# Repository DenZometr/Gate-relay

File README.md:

Реле для контроля и управления автоматическими воротами.

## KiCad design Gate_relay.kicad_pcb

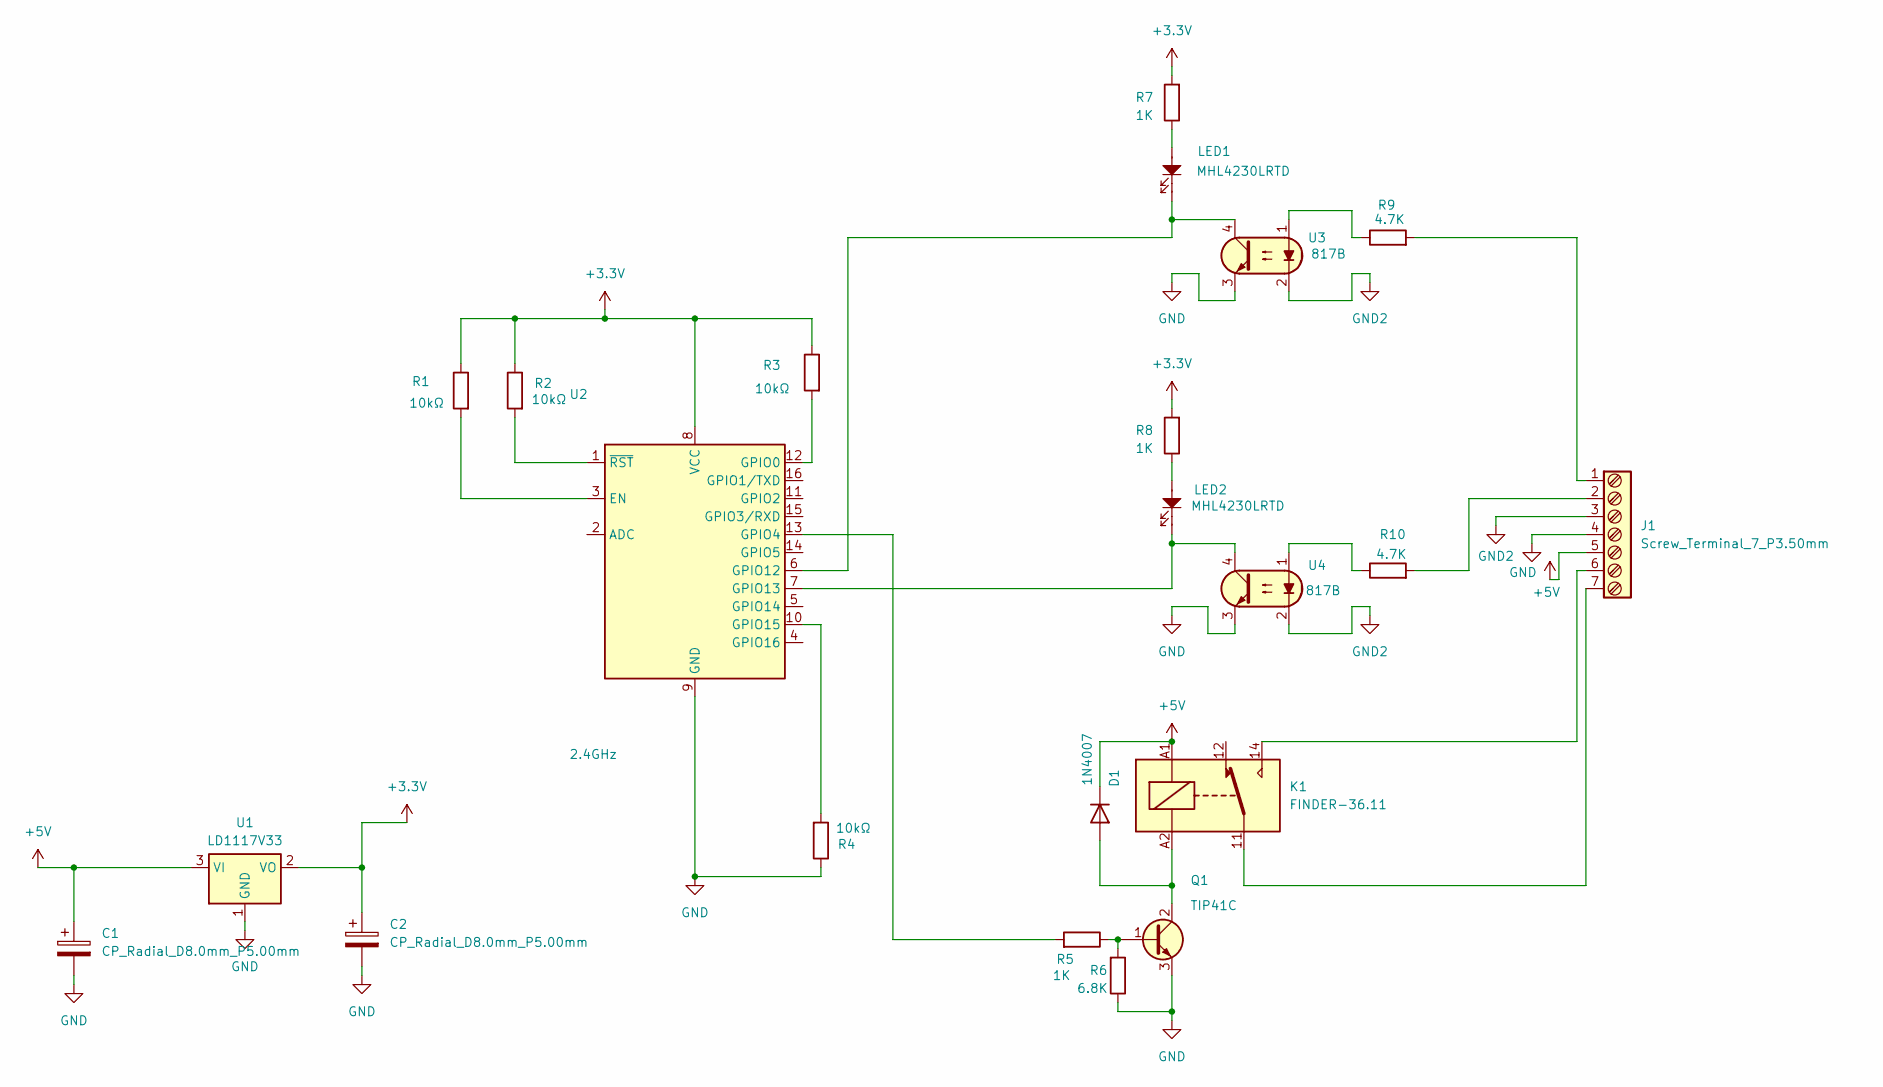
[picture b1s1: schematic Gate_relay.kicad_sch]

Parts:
C1, C2: CP_Radial_D8.0mm_P5.00mm
D1: 1N4007; D_A-405_P5.08mm_Vertical_AnodeUp; VOLTAGE - FORWARD(VF@IF) 1.1V@1A; VOLTAGE - DC REVERSE(VR) 1kV; MANUFACTURER PART 1N4007; LCSC PART NAME 1kV 1A
J1: Screw_Terminal_7_P3.50mm; TerminalBlock_Xinya_XY308-2.54-7P_1x07_P2.54mm_Horizontal
K1: FINDER-36.11; Relay_SPDT_Finder_36.11
LED1, LED2: MHL4230LRTD; LED_D5.0mm; FORWARD VOLTAGE (VF) 1.8V~2.4V; MANUFACTURER PART MHL4230LRTD; LCSC PART NAME F4直插红色雾状发红色光
Q1: TIP41C; TO-220-3_Vertical_BCE; MANUFACTURER PART TIP41C; LCSC PART NAME NPN 电流:6A 耐压:100V
R1, R2, R3, R4: 10kΩ; R_Axial_DIN0204_L3.6mm_D1.6mm_P2.54mm_Vertical; TOLERANCE ±1%; VOLTAGE-SUPPLY(MAX) 250V; MANUFACTURER PART MFR0W4F1002A50; LCSC PART NAME 10kΩ ±1% 250mW 金属膜电阻 铜脚，圆柱状直插
R5, R7: 1K; R_Axial_DIN0204_L3.6mm_D1.6mm_P2.54mm_Vertical
R6: 6.8K; R_Axial_DIN0204_L3.6mm_D1.6mm_P2.54mm_Vertical
R8: 1K; R_Axial_DIN0204_L3.6mm_D1.6mm_P7.62mm_Horizontal
R9, R10: 4.7K; R_Axial_DIN0204_L3.6mm_D1.6mm_P2.54mm_Vertical
U1: LD1117V33; TO-220-3_Vertical
U2: 2.4GHz; ESP-07; OPERATING VOLTAGE 3.3V; MANUFACTURER PART ESP-07; LCSC PART NAME 802.11b/g/n模块
U3, U4: 817B; DIP-4_W7.62mm_LongPads; VOLTAGE - FORWARD(VF) 1.2V; ISOLATION VOLTAGE(VRMS) 5kV; MANUFACTURER PART 817B; LCSC PART NAME DC输入

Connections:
+3.3V: C2.1, R1.2, R2.2, R3.2, R7.1, R8.1, U1.2 (VO), U2.8 (VCC)
+5V: C1.1, D1.1 (K), J1.5, K1.A1, U1.3 (VI)
GND: C1.2, C2.2, J1.4, Q1.3 (E), R4.2, R6.2, U1.1 (GND), U2.9 (GND), U3.3, U4.3
GND2: J1.3, U3.2, U4.2
unnamed: D1.2 (A), K1.A2, Q1.2 (C)
unnamed: J1.1, R9.1
unnamed: J1.2, R10.1
unnamed: J1.6, K1.14
unnamed: J1.7, K1.11
unnamed: LED1.2, R7.2
unnamed: LED2.2, R8.2
unnamed: Q1.1 (B), R5.2, R6.1
unnamed: R9.2, U3.1
unnamed: R10.2, U4.1
unnamed: R1.1, U2.3 (EN)
unnamed: R3.1, U2.12 (GPIO0)
unnamed: R5.1, U2.13 (GPIO4)
unnamed: LED1.1, U2.6 (GPIO12), U3.4
unnamed: LED2.1, U2.7 (GPIO13), U4.4
unnamed: R4.1, U2.10 (GPIO15)
unnamed: R2.1, U2.1 (~RST)

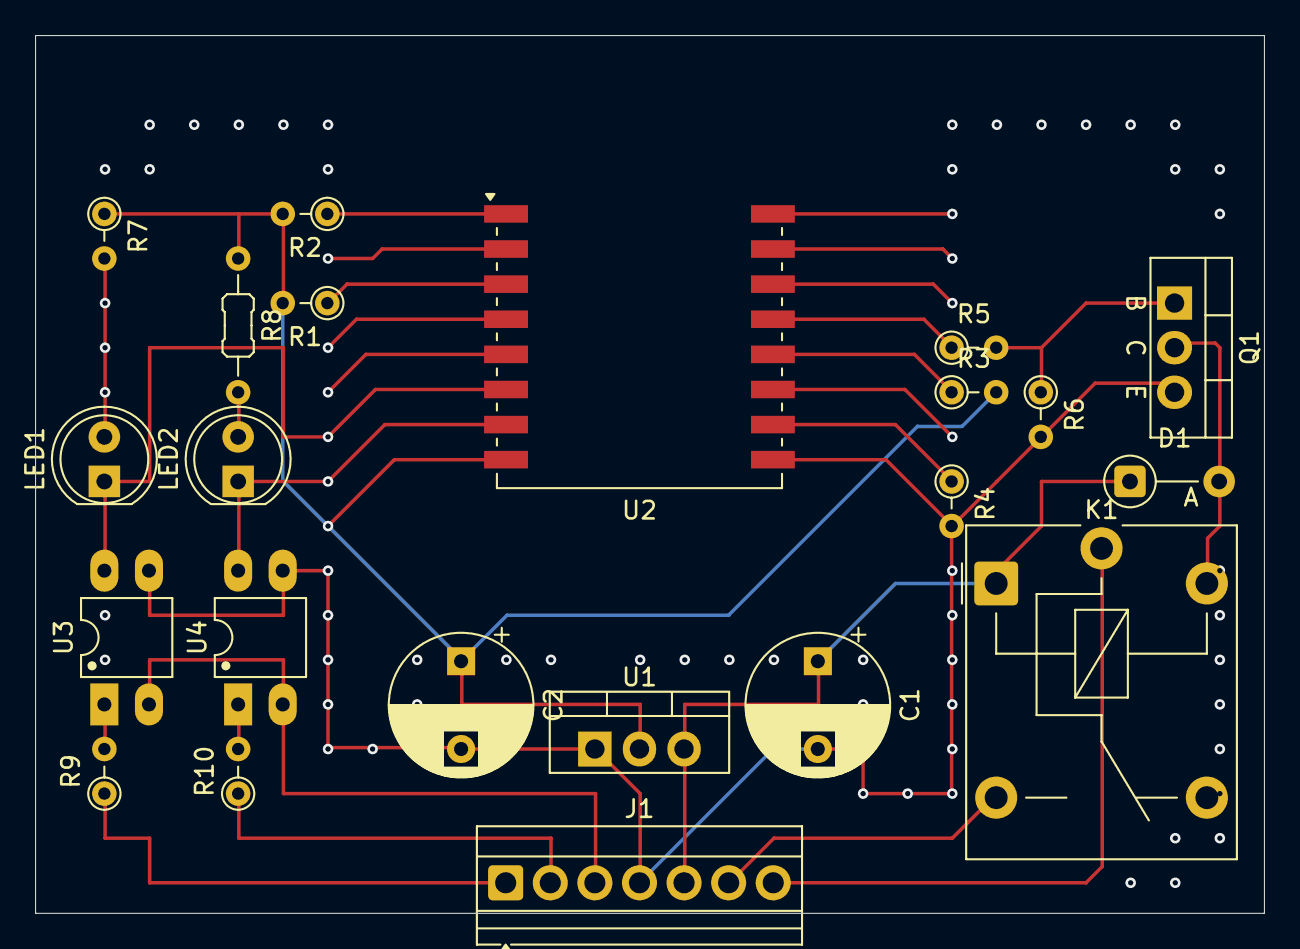
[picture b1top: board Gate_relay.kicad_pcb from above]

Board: 2 copper layers, 70.0 x 50.0 mm, 22 parts (0 on the bottom side), 21 nets.

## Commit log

2026-04-08 Add files via upload
    Прошивка для ESPHome для реле ворот.
